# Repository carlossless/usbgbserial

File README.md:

# usbgbserial

> ⚠️ This project is very much work in progress. Most things are either not done or don't fully work. ⚠️

A USB to [Game Link Cable](https://en.wikipedia.org/wiki/Game_Link_Cable) interface.

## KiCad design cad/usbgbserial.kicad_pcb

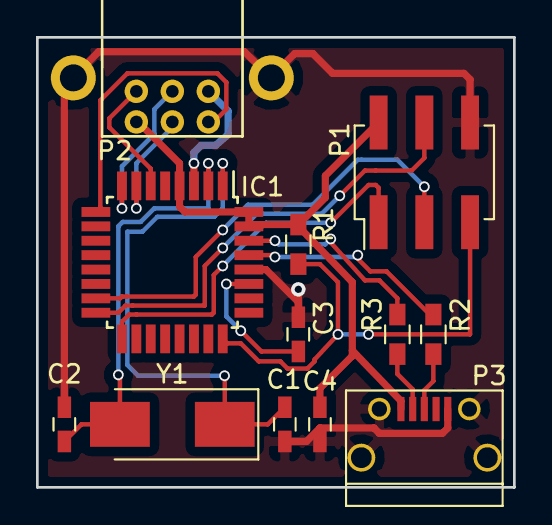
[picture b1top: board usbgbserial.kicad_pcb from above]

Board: 2 copper layers, 26.5 x 25.0 mm, 12 parts (0 on the bottom side), 17 nets.

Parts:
C1, C2: 22pF; C_0603_HandSoldering
C3: 1uF; C_0603_HandSoldering
C4: 100nF; C_0603_HandSoldering
IC1: ATMEGA32U2; TQFP-32_7x7mm_Pitch0.8mm
P1: AVR_ISP; Pin_Header_Straight_2x03_Pitch2.54mm_SMD
P2: GB_SERIAL; gb-serial
P3: USB_OTG; USB_Micro-B
R1: 10K; R_0603_HandSoldering
R2, R3: 22; R_0603_HandSoldering
Y1: 16Mhz; Crystal_SMD_0603-2pin_6.0x3.5mm_HandSoldering

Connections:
GND: C1.2, C2.2, C3.2, C4.2, IC1.3, IC1.28, P1.6, P2.6, P2.7, P3.5, P3.6
MISO: IC1.17, P1.1
MOSI: IC1.16, P1.4
unnamed: C1.1, IC1.1, Y1.1
unnamed: C2.1, IC1.2, Y1.2
unnamed: C3.1, IC1.27
unnamed: IC1.6, P2.2
unnamed: IC1.7, P2.3
unnamed: IC1.8, P2.4
unnamed: IC1.9, P2.5
unnamed: IC1.29, R2.1
unnamed: IC1.30, R3.1
unnamed: P3.2, R3.2
unnamed: P3.3, R2.2
RESET: IC1.24, P1.5, R1.1
SCK: IC1.15, P1.3
VCC: C4.1, IC1.4, IC1.31, IC1.32, P1.2, P2.1, P3.1, R1.2

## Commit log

2017-04-03 First PCB version
2017-04-28 LUDA, bootloader, makefile update
2020-04-21 an example pokemon mew trader
2020-04-25 readmes and pokemon firmware
2020-04-25 main readme update
2020-04-25 readme fixup
2020-04-26 readme and video update
2020-04-26 switched video iframe with link
